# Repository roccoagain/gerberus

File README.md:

# Gerberus

Gerberus checks a PCB design for electrical bugs before you order it: parts pushed past their datasheet limits,
missing protection, swapped pins, parts you can't buy, and bad USB routing. It reads KiCad designs.

## Install

Gerberus is built from source. With [Rust](https://rustup.rs) and git installed:

```sh
git clone https://github.com/roccoagain/gerberus
cd gerberus
cargo install --locked --path .
```

That puts the `gerberus` command in `~/.cargo/bin`. To update, run `git pull` and the same `cargo install` again.

Three commands need another program installed: `gerberus stress` and `gerberus signal` need [ngspice](https://ngspice.sourceforge.io/),
and `gerberus datasheet verify` needs poppler's `pdftotext`. More in [docs/install.md](docs/install.md).

## Quick start

Try it on one of the example boards in the clone:

```sh
cd tests/fixtures/sniffer
gerberus check sniffer.kicad_sch
```

It prints each problem it found, then a count:

```text
error[abs-max]: U1.CE reaches -5.5 V, past the minimum of -0.3 V
  --> U1.CE (+5V), in fault "VIN reversed"
   = help: add a divider, clamp or series resistor, or choose a part rated higher
...
error: 2 errors, 3 warnings, 8 unknown, 102 passed
```

An **error** means a part can be damaged or the board won't work; a **warning** is a risk worth a look. Each one
says what is wrong, where, and how to fix it. **Unknown** means Gerberus couldn't
decide, usually because a part has no part file yet; it never counts as a pass. Add `--all` to list those and the
passes too, and `--verbose` to see the numbers each finding compared, the datasheet pages they came from and how each
net got its voltage range. `gerberus explain abs-max` says what a rule checks and why ([all rules](docs/rules.md)).
The sniffer's 2 errors
are its supply connected backwards, which damages the regulator; its warnings are a regulator input that can sag
below what it needs and headers with no ESD protection.

To see the findings on the drawings, add `--html report.html`: one web page with the schematic and board, each
finding ringed on its part. It needs KiCad's `kicad-cli` on the PATH. [More](docs/html-report.md)

On your own board, point it at the root schematic (`.kicad_sch`). `check` runs
straight away, but without knowing what plugs into the board it can only take the net named GND as 0 V, so most
nets come out unknown. Run `gerberus init` on the schematic to start an `inputs.toml` that says what voltages
arrive on each connector pin (for example, 3.6 to 5.5 V on J1 pin 1). It guesses what it can from net names and
marks each guess for you to check; see [the format](parts/README.md#board-inputs).

To see what to add first, run `gerberus doctor` on the schematic. It lists every part with no part file, every
connector pin nothing describes, and every gap in a part file, ranked by how many unknown results each one
settles. [More](docs/doctor.md)

## What it checks

| Command | What it checks |
| --- | --- |
| `gerberus check` | Every pin against its datasheet limits at its net's worst-case voltage, TVS diodes, capacitor voltage, resistor power, undriven inputs, regulator headroom, junction temperature, ESD protection on connectors, and a supply connected backwards. [More](docs/voltage-checks.md) |
| `gerberus diff` | What changed between two revisions, or against a git tag: parts, connections made or broken, and new or fixed findings. [More](docs/diff.md) |
| `gerberus stress` | Plugging the board in, simulated in SPICE with part tolerances: voltage spikes on every pin. [More](docs/stress.md) |
| `gerberus signal` | Audio and analog signals through the board in SPICE: where an op-amp clips, and what each IC pin sees. [More](docs/signal.md) |
| `gerberus bringup` | A first-power checklist: which supply to connect first, the current limit to set, and the voltage to expect on each rail and where to probe it. [More](docs/bringup.md) |
| `gerberus pinout` | Symbol pins, footprint pads and the datasheet pin table agree. [More](docs/pinout.md) |
| `gerberus bom` | Every part is in stock at LCSC and still listed, with stocked equivalents for short resistors and capacitors. [More](docs/bom.md) |
| `gerberus traces` | Every track wide enough for its net's worst-case current (IPC-2221), every power pin still at its minimum after the copper's voltage drop, a decoupling capacitor near every power pin, no signal crossing a plane split, each switcher's input loop small, SPI/I²S lines short enough for their edges, and thermal reliefs, tombstoning and fiducials for assembly. [More](docs/traces.md) |
| `gerberus si` | USB 2.0 pairs on the board: impedance, skew, vias, stubs, reference planes, and a simulated eye diagram. [More](docs/usb-si.md) |
| `gerberus datasheet` | A part file against its datasheet, value by value. [More](docs/datasheets.md) |

Part limits come from a built-in library of part files, each value cited to its datasheet page. A part with no
part file comes out UNKNOWN rather than PASS. To add one, start it with `gerberus part new <schematic> <reference>`
and fill it in from the datasheet; see [parts/README.md](parts/README.md).

For an AI agent working in a board's repository, `gerberus skill install` adds two skills there: `check-board`
(set up inputs.toml, follow `gerberus doctor`, run the checks) and `datasheet-to-part` (read a datasheet into a
part file, verified against its pages and read twice).

A finding the designers accept on purpose goes in a `waivers.toml` next to the schematic, with the reason; see
[waivers](docs/waivers.md).

Run `gerberus --help` for every command and option.

## Links

- [Docs](docs/README.md): every check in detail.
- [Part file format](parts/README.md).
- [Roadmap](ROADMAP.md).
- [Developing Gerberus](docs/development.md): tests and CI.
- [Example boards](https://github.com/roccoagain/hardware).

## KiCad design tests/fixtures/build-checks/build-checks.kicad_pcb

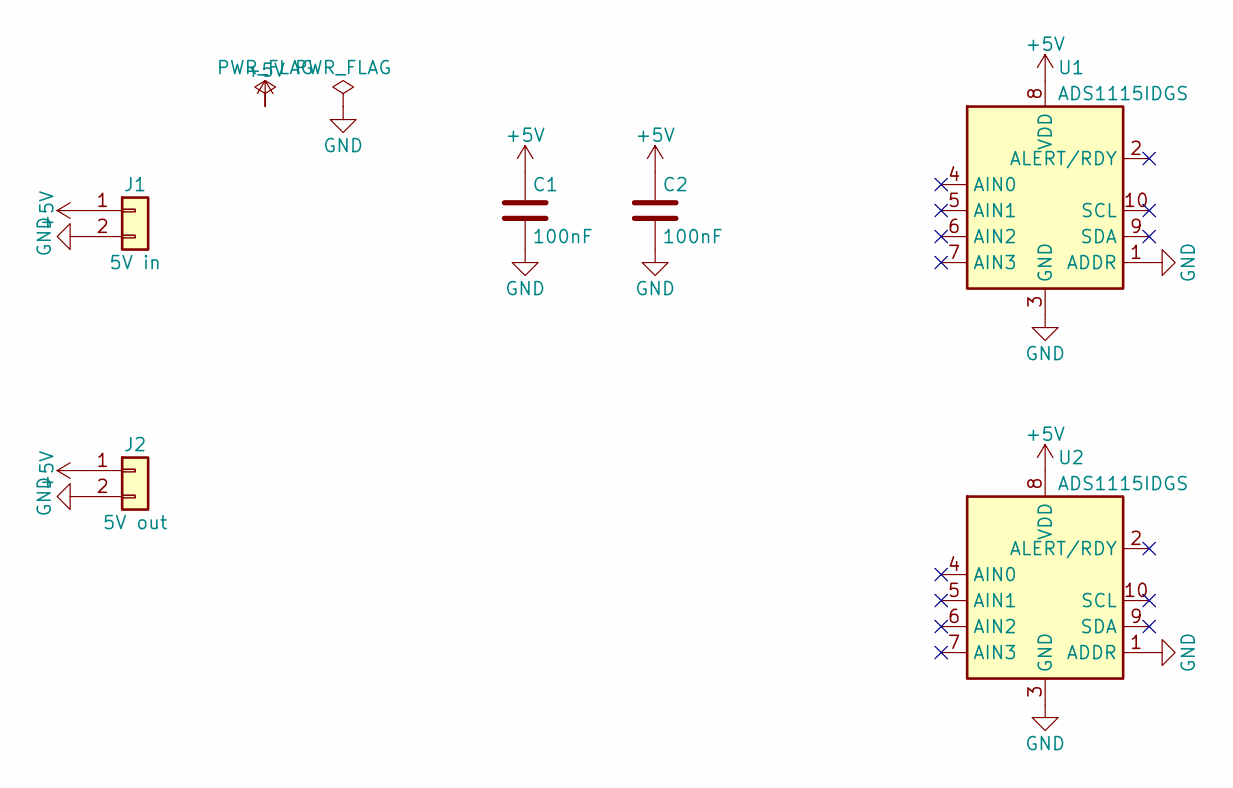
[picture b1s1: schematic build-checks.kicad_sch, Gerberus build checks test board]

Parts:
C1, C2: 100nF; C_0402_1005Metric
J1: 5V in; PinHeader_1x02_P2.54mm_Vertical
J2: 5V out; PinHeader_1x02_P2.54mm_Vertical
U1, U2: ADS1115IDGS; TSSOP-10_3x3mm_P0.5mm

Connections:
+5V: C1.1, C2.1, J1.1, J2.1, U1.8 (VDD), U2.8 (VDD)
GND: C1.2, C2.2, J1.2, J2.2, U1.1 (ADDR), U1.3 (GND), U2.1 (ADDR), U2.3 (GND)

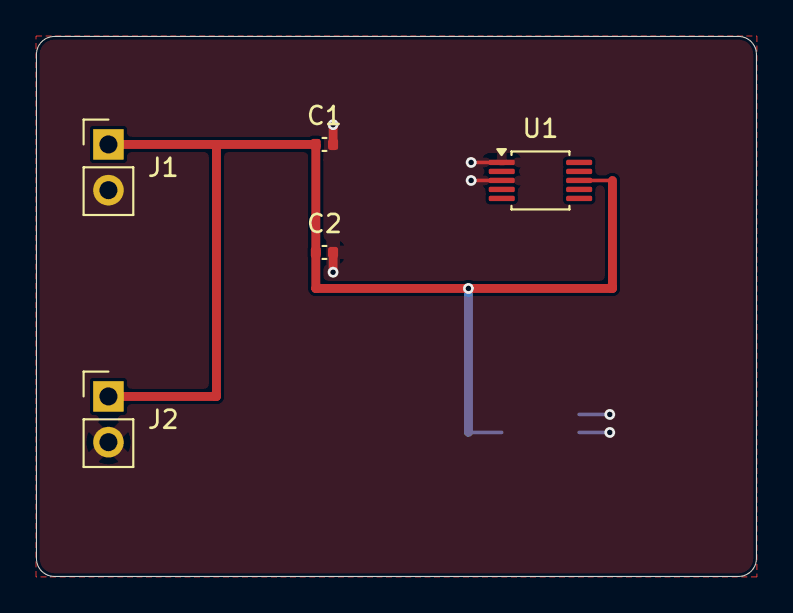
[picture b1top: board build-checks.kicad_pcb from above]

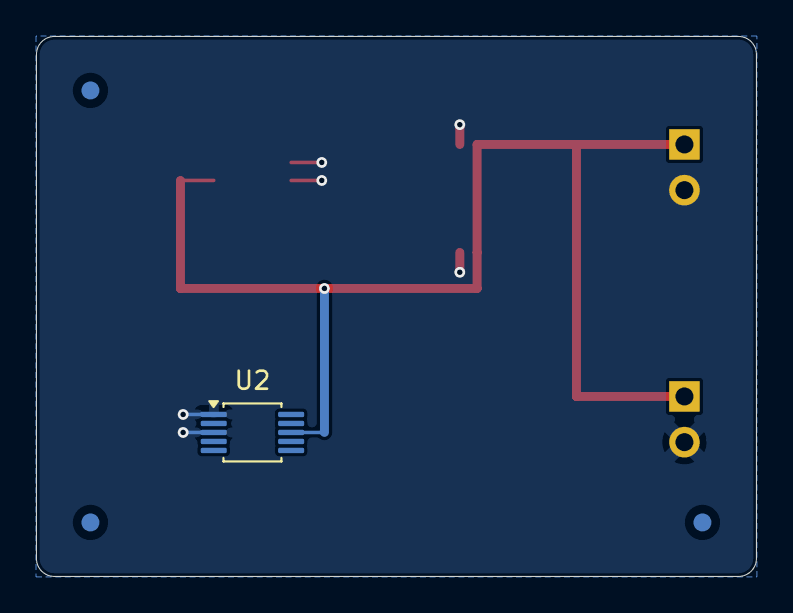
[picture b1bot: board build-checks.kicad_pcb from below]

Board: 2 copper layers, 40.0 x 30.0 mm, 9 parts (4 on the bottom side), 2 nets.

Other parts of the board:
FID1, FID2, FID3: Fiducial_1mm_Mask2mm

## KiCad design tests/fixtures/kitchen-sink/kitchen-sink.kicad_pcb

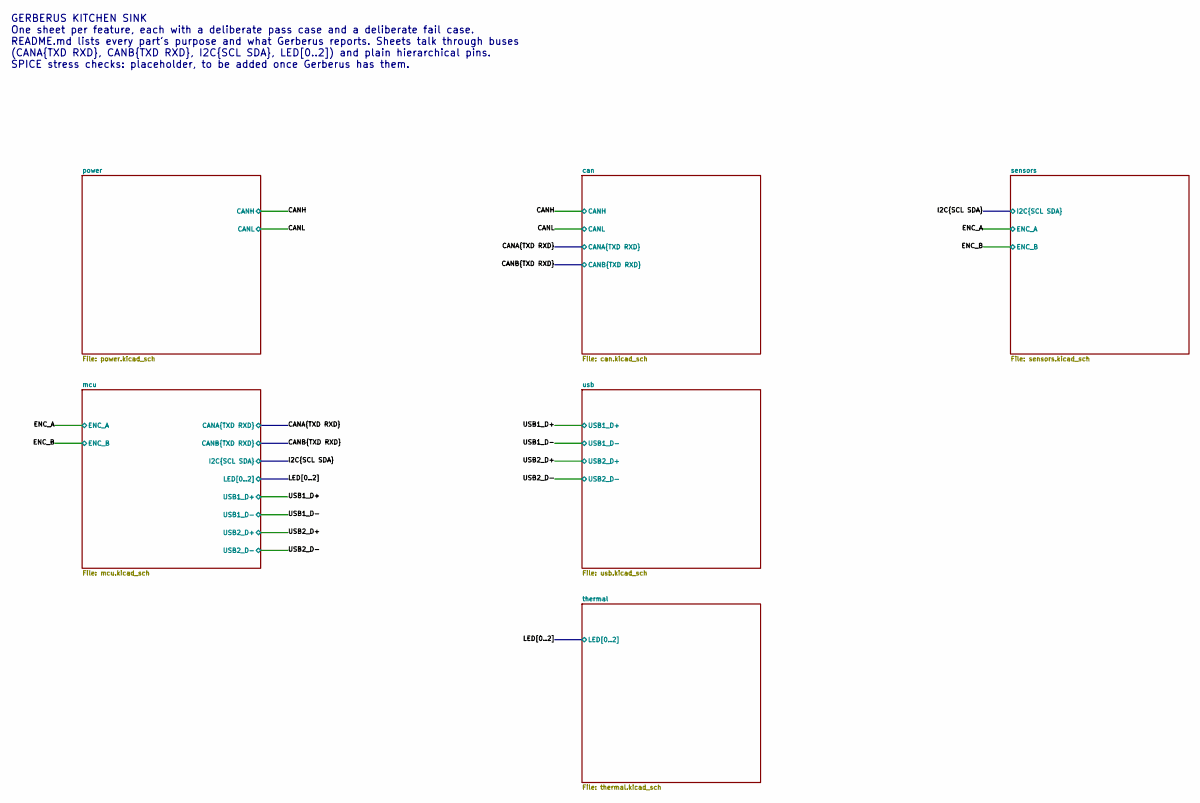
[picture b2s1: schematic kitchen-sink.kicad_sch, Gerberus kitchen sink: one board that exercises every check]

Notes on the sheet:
GERBERUS KITCHEN SINK One sheet per feature, each with a deliberate pass case and a deliberate fail case. README.md lists every part's purpose and what Gerberus reports. Sheets talk through buses (CANA{TXD RXD}, CANB{TXD RXD}, I2C{SCL SDA}, LED[0..2]) and plain hierarchical pins. SPICE stress check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

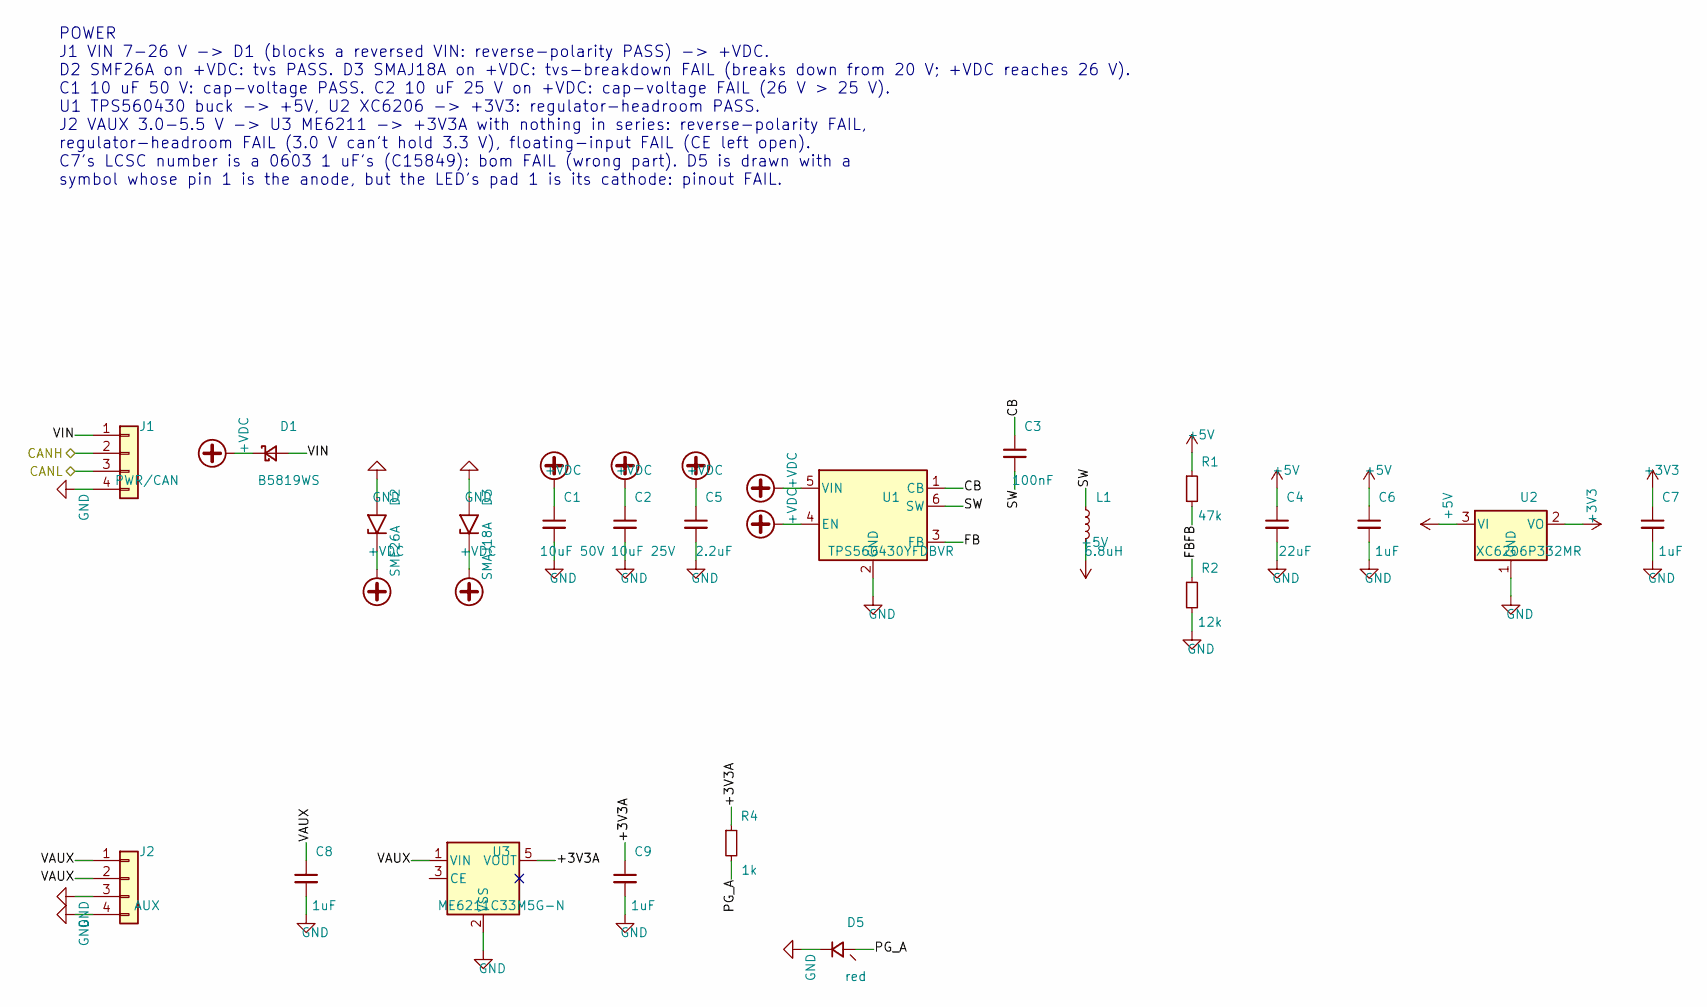
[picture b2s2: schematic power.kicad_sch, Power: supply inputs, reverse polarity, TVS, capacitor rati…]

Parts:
C1: 10uF 50V; C_0805_2012Metric; MPN GRM21BR61H106KE43L; LCSC C440198
C2: 10uF 25V; C_0805_2012Metric; MPN CL21A106KAYNNNE; LCSC C15850
C3: 100nF; C_0402_1005Metric; MPN CL05B104KO5NNNC; LCSC C1525
C4: 22uF; C_0805_2012Metric; MPN CL21A226MAQNNNE; LCSC C45783
C5: 2.2uF; C_0805_2012Metric; MPN CC0805KKX7R9BB225; LCSC C125847
C6, C8, C9: 1uF; C_0402_1005Metric; MPN CL05A105KA5NQNC; LCSC C52923
C7: 1uF; C_0402_1005Metric; MPN CL05A105KA5NQNC; LCSC C15849
D1: B5819WS; D_SOD-323; MPN B5819WS; LCSC C22624
D2: SMF26A; D_SOD-123F; MPN SMF26A; LCSC C123789
D3: SMAJ18A; D_SMA; MPN SMAJ18A; LCSC C173513
D5: red; LED_0603_1608Metric; MPN KT-0603R; LCSC C2286
J1: PWR/CAN; JST_GH_SM04B-GHS-TB_1x04-1MP_P1.25mm_Horizontal; MPN SM04B-GHS-TB(LF)(SN); LCSC C189895
J2: AUX; JST_SH_SM04B-SRSS-TB_1x04-1MP_P1.00mm_Horizontal; MPN SM04B-SRSS-TB(LF)(SN); LCSC C160404
L1: 6.8uH; L_Changjiang_FNR4030S; MPN FNR4030S6R8MT; LCSC C167876
R1: 47k; R_0402_1005Metric; MPN 0402WGF4702TCE; LCSC C25792
R2: 12k; R_0402_1005Metric; MPN 0402WGF1202TCE; LCSC C25752
R4: 1k; R_0603_1608Metric; MPN 0603WAF1001T5E; LCSC C21190
U1: TPS560430YFDBVR; SOT-23-6; MPN TPS560430YFDBVR; LCSC C962155
U2: XC6206P332MR; SOT-23-3; MPN XC6206P332MR-G; LCSC C5446
U3: ME6211C33M5G-N; SOT-23-5; MPN ME6211C33M5G-N; LCSC C82942

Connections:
+3V3: C7.1, U2.2 (VO); also elsewhere on the board
+5V: C4.1, C6.1, L1.2, R1.1, U2.3 (VI); also elsewhere on the board
+VDC: C1.1, C2.1, C5.1, D1.1 (K), D2.1 (A1), D3.1 (A1), U1.4 (EN), U1.5 (VIN); also elsewhere on the board
/CANH: J1.2; also elsewhere on the board
/CANL: J1.3; also elsewhere on the board
/power/+3V3A: C9.1, R4.1, U3.5 (VOUT)
/power/CB: C3.1, U1.1 (CB)
/power/FB: R1.2, R2.1, U1.3 (FB)
/power/PG_A: D5.1 (A), R4.2
/power/SW: C3.2, L1.1, U1.6 (SW)
/power/VAUX: C8.1, J2.1, J2.2, U3.1 (VIN)
/power/VIN: D1.2 (A), J1.1
GND: C1.2, C2.2, C4.2, C5.2, C6.2, C7.2, C8.2, C9.2, D2.2 (A2), D3.2 (A2), D5.2 (K), J1.4, J2.3, J2.4, R2.2, U1.2 (GND), U2.1 (GND), U3.2 (VSS); also elsewhere on the board

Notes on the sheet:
POWER J1 VIN 7-26 V -> D1 (blocks a reversed VIN: reverse-polarity PASS) -> +VDC. D2 SMF26A on +VDC: tvs PASS. D3 SMAJ18A on +VDC: tvs-breakdown FAIL (breaks down from 20 V; +VDC reaches 26 V). C1 10 uF 50 V: cap-voltage PASS. C2 10 uF 25 V on +VDC: cap-voltage FAIL (26 V > 25 V). U1 TPS560430 buck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

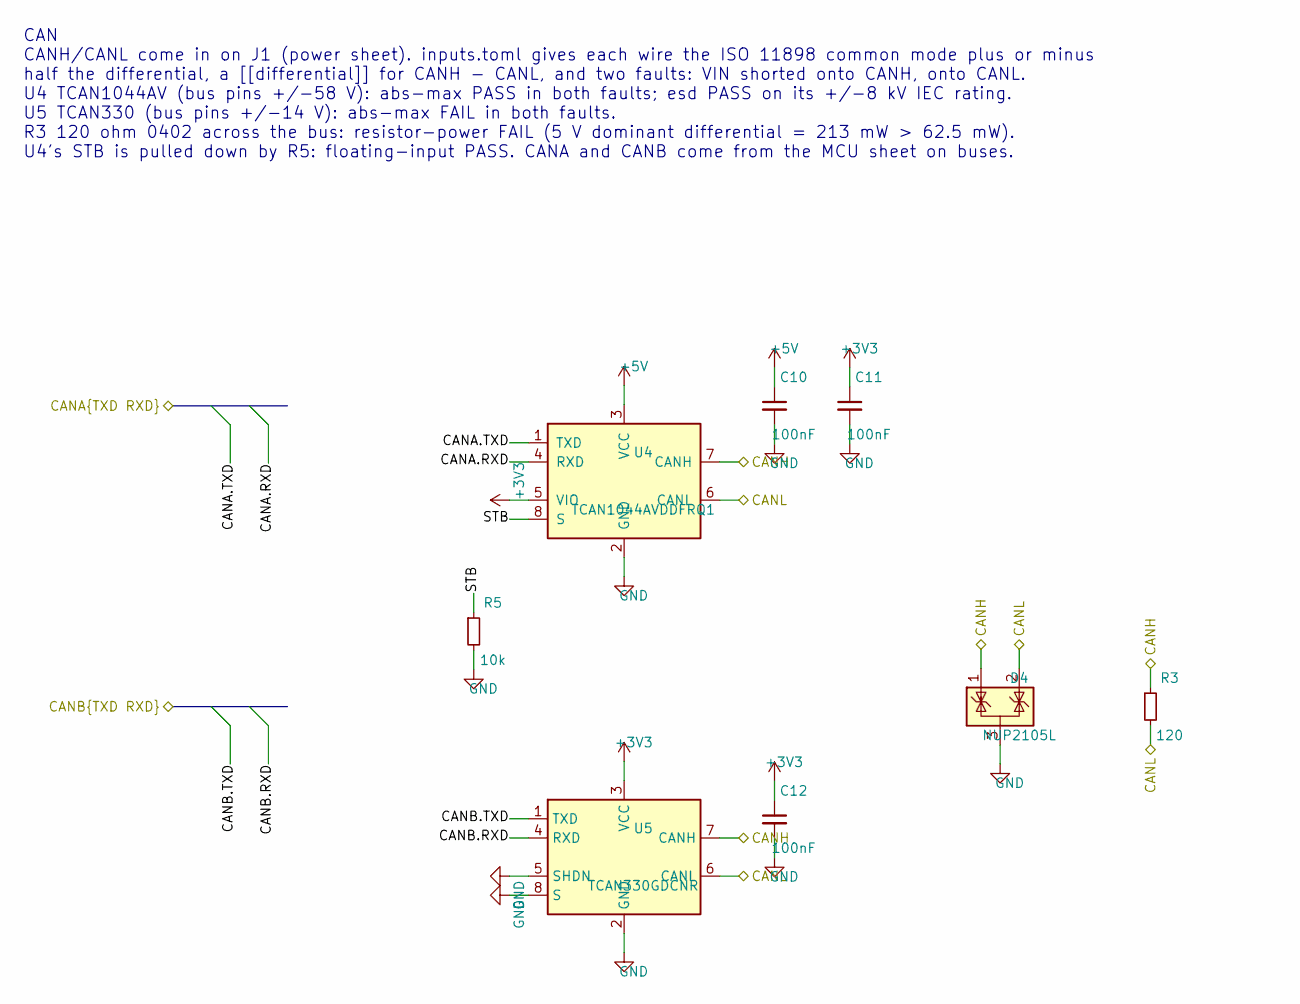
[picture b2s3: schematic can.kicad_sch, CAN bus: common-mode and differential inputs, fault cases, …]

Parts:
C10, C11, C12: 100nF; C_0402_1005Metric; MPN CL05B104KO5NNNC; LCSC C1525
D4: NUP2105L; SOT-23; MPN NUP2105LT1G; LCSC C14486
R3: 120; R_0402_1005Metric; MPN 0402WGF1200TCE; LCSC C25079
R5: 10k; R_0402_1005Metric; MPN 0402WGF1002TCE; LCSC C25744
U4: TCAN1044AVDDFRQ1; SOT-23-8; MPN TCAN1044AVDDFRQ1; LCSC C3236207
U5: TCAN330GDCNR; SOT-23-8; MPN TCAN330GDCNR; LCSC C191006

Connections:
+3V3: C11.1, C12.1, U4.5 (VIO), U5.3 (VCC); also elsewhere on the board
+5V: C10.1, U4.3 (VCC); also elsewhere on the board
/CANA.RXD: U4.4 (RXD); also elsewhere on the board
/CANA.TXD: U4.1 (TXD); also elsewhere on the board
/CANB.RXD: U5.4 (RXD); also elsewhere on the board
/CANB.TXD: U5.1 (TXD); also elsewhere on the board
/CANH: D4.1 (K), R3.1, U4.7 (CANH), U5.7 (CANH); also elsewhere on the board
/CANL: D4.2 (K), R3.2, U4.6 (CANL), U5.6 (CANL); also elsewhere on the board
/can/STB: R5.1, U4.8 (S)
GND: C10.2, C11.2, C12.2, D4.3 (A), R5.2, U4.2 (GND), U5.2 (GND), U5.5 (SHDN), U5.8 (S); also elsewhere on the board

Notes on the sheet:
CAN CANH/CANL come in on J1 (power sheet). inputs.toml gives each wire the ISO 11898 common mode plus or minus half the differential, a [[differential]] for CANH - CANL, and two faults: VIN shorted onto CANH, onto CANL. U4 TCAN1044AV (bus pins +/-58 V): abs-max PASS in both faults; esd PASS on its 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

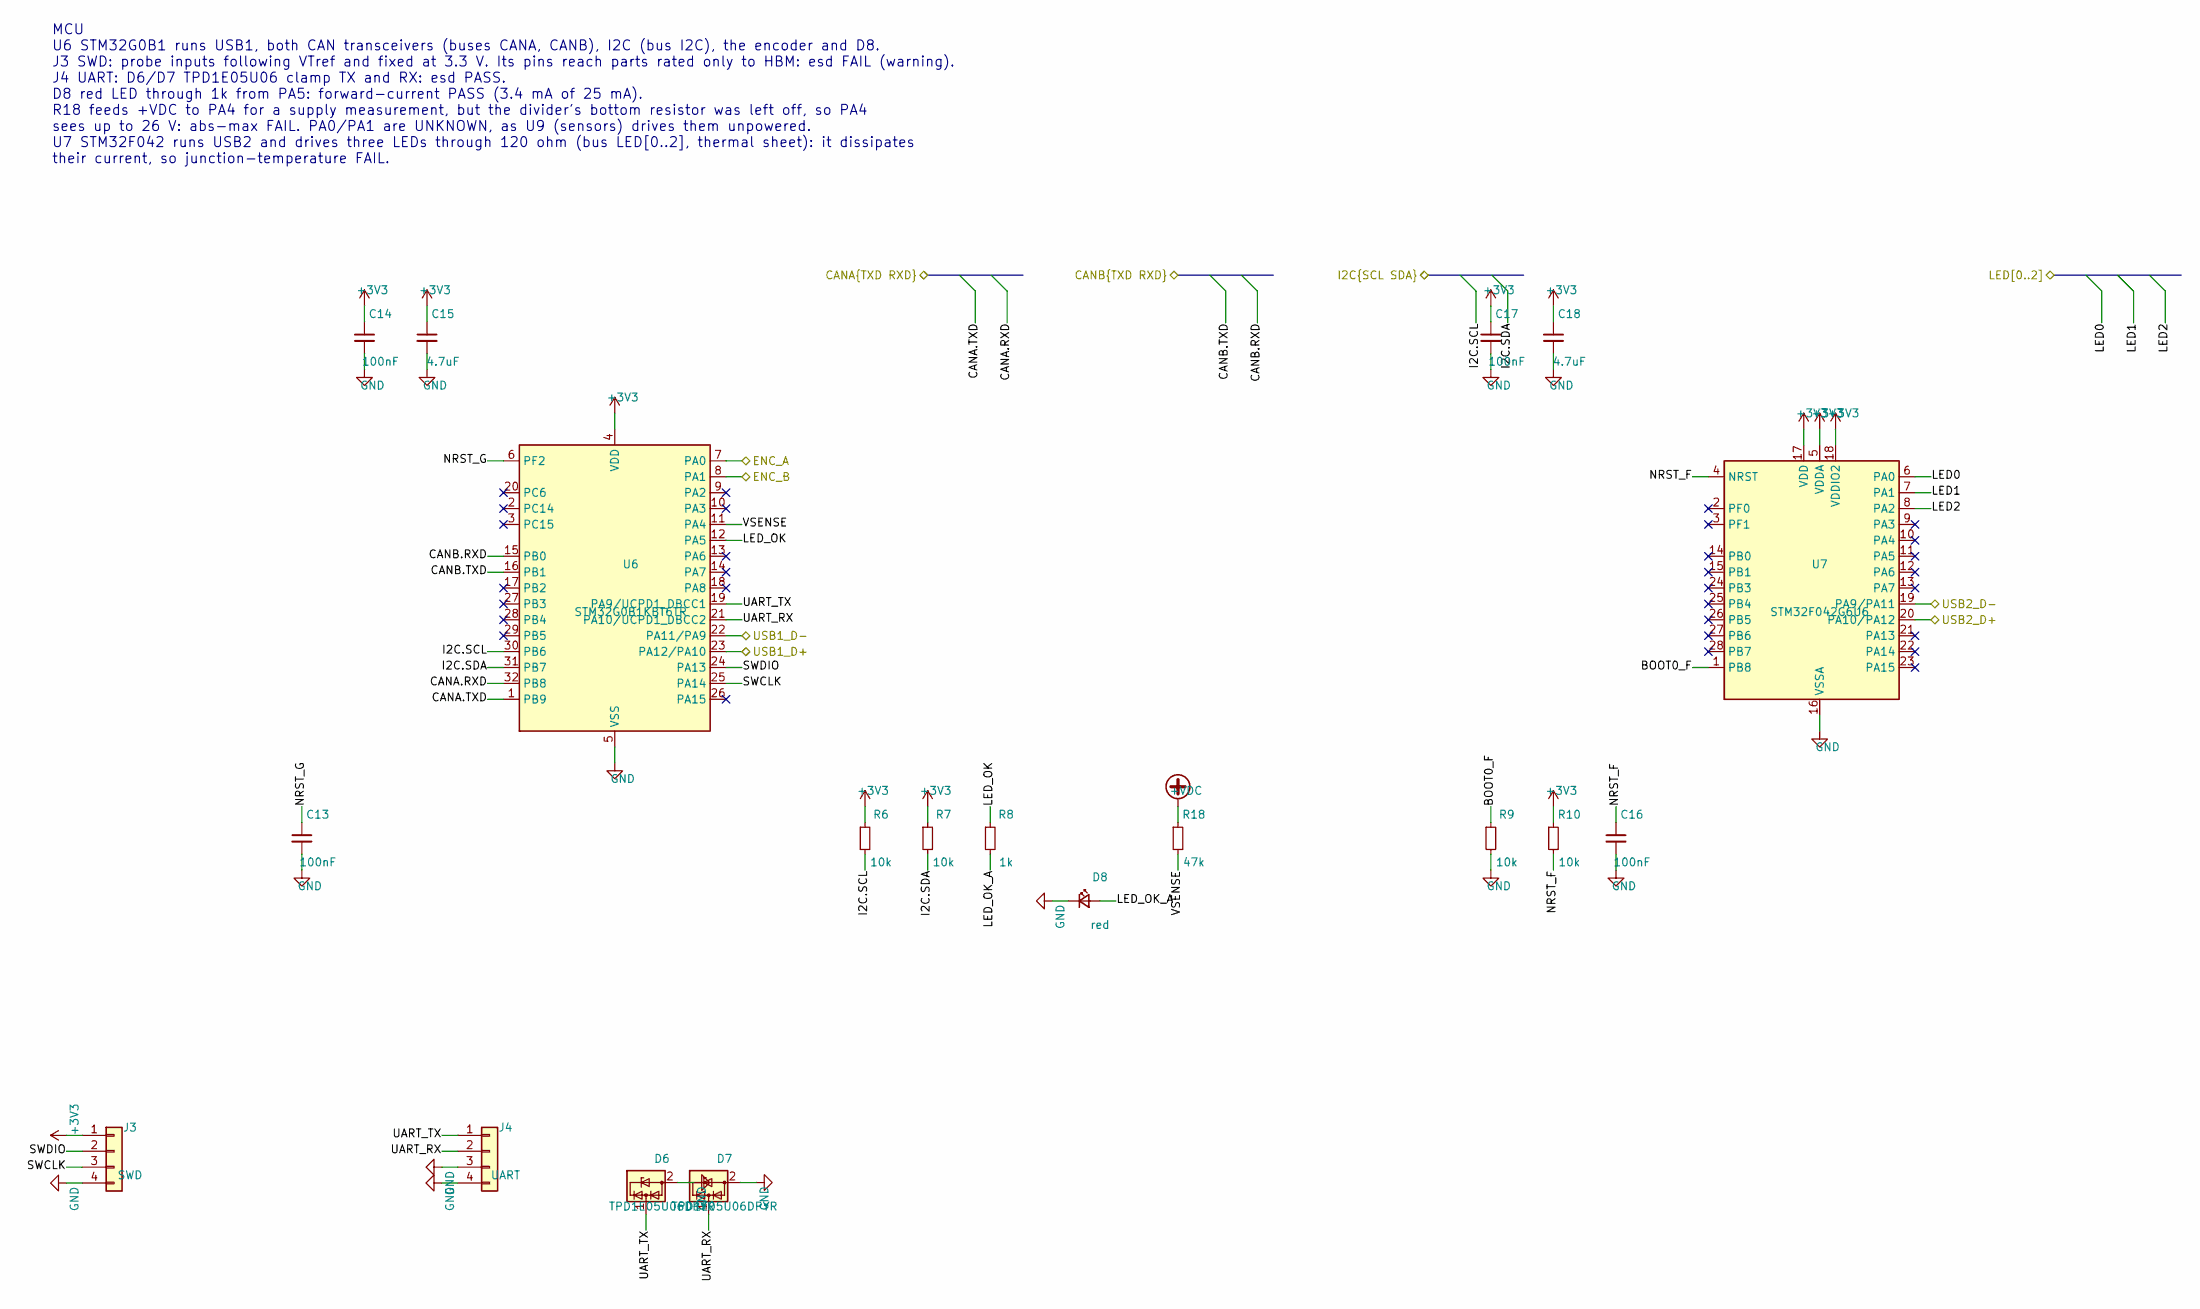
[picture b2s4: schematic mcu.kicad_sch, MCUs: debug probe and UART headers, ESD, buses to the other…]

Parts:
C13, C14, C16, C17: 100nF; C_0402_1005Metric; MPN CL05B104KO5NNNC; LCSC C1525
C15, C18: 4.7uF; C_0603_1608Metric; MPN CL10A475KO8NNNC; LCSC C19666
D6, D7: TPD1E05U06DPYR; Texas_DPY0002A_0.6x1mm_P0.65mm; MPN TPD1E05U06DPYR; LCSC C436349
D8: red; LED_0603_1608Metric; MPN KT-0603R; LCSC C2286
J3: SWD; JST_SH_SM04B-SRSS-TB_1x04-1MP_P1.00mm_Horizontal; MPN SM04B-SRSS-TB(LF)(SN); LCSC C160404
J4: UART; JST_SH_SM04B-SRSS-TB_1x04-1MP_P1.00mm_Horizontal; MPN SM04B-SRSS-TB(LF)(SN); LCSC C160404
R6, R7, R9, R10: 10k; R_0603_1608Metric; MPN 0603WAF1002T5E; LCSC C25804
R8: 1k; R_0603_1608Metric; MPN 0603WAF1001T5E; LCSC C21190
R18: 47k; R_0402_1005Metric; MPN 0402WGF4702TCE; LCSC C25792
U6: STM32G0B1KBT6TR; LQFP-32_7x7mm_P0.8mm; MPN STM32G0B1KBT6TR; LCSC C7021416
U7: STM32F042G6U6; QFN-28_4x4mm_P0.5mm; MPN STM32F042G6U6TR; LCSC C2971720

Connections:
+3V3: C14.1, C15.1, C17.1, C18.1, J3.1, R6.1, R7.1, R10.1, U6.4 (VDD), U7.5 (VDDA), U7.17 (VDD), U7.18 (VDDIO2); also elsewhere on the board
+VDC: R18.1; also elsewhere on the board
/CANA.RXD: U6.32 (PB8); also elsewhere on the board
/CANA.TXD: U6.1 (PB9); also elsewhere on the board
/CANB.RXD: U6.15 (PB0); also elsewhere on the board
/CANB.TXD: U6.16 (PB1); also elsewhere on the board
/ENC_A: U6.7 (PA0); also elsewhere on the board
/ENC_B: U6.8 (PA1); also elsewhere on the board
/I2C.SCL: R6.2, U6.30 (PB6); also elsewhere on the board
/I2C.SDA: R7.2, U6.31 (PB7); also elsewhere on the board
/LED0: U7.6 (PA0); also elsewhere on the board
/LED1: U7.7 (PA1); also elsewhere on the board
/LED2: U7.8 (PA2); also elsewhere on the board
/USB1_D+: U6.23 (PA12/PA10); also elsewhere on the board
/USB1_D-: U6.22 (PA11/PA9); also elsewhere on the board
/USB2_D+: U7.20 (PA10/PA12); also elsewhere on the board
/USB2_D-: U7.19 (PA9/PA11); also elsewhere on the board
/mcu/BOOT0_F: R9.1, U7.1 (PB8)
/mcu/LED_OK: R8.1, U6.12 (PA5)
/mcu/LED_OK_A: D8.2 (A), R8.2
/mcu/NRST_F: C16.1, R10.2, U7.4 (NRST)
/mcu/NRST_G: C13.1, U6.6 (PF2)
/mcu/SWCLK: J3.3, U6.25 (PA14)
/mcu/SWDIO: J3.2, U6.24 (PA13)
/mcu/UART_RX: D7.1 (I/O), J4.2, U6.21 (PA10/UCPD1_DBCC2)
/mcu/UART_TX: D6.1 (I/O), J4.1, U6.19 (PA9/UCPD1_DBCC1)
/mcu/VSENSE: R18.2, U6.11 (PA4)
GND: C13.2, C14.2, C15.2, C16.2, C17.2, C18.2, D6.2 (GND), D7.2 (GND), D8.1 (K), J3.4, J4.3, J4.4, R9.2, U6.5 (VSS), U7.16 (VSSA); also elsewhere on the board

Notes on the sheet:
MCU U6 STM32G0B1 runs USB1, both CAN transceivers (buses CANA, CANB), I2C (bus I2C), the encoder and D8. J3 SWD: probe inputs following VTref and fixed at 3.3 V. Its pins reach parts rated only to HBM: esd FAIL (warning). J4 UART: D6/D7 TPD1E05U06 clamp TX and RX: esd PASS. D8 red LED through 1k fr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

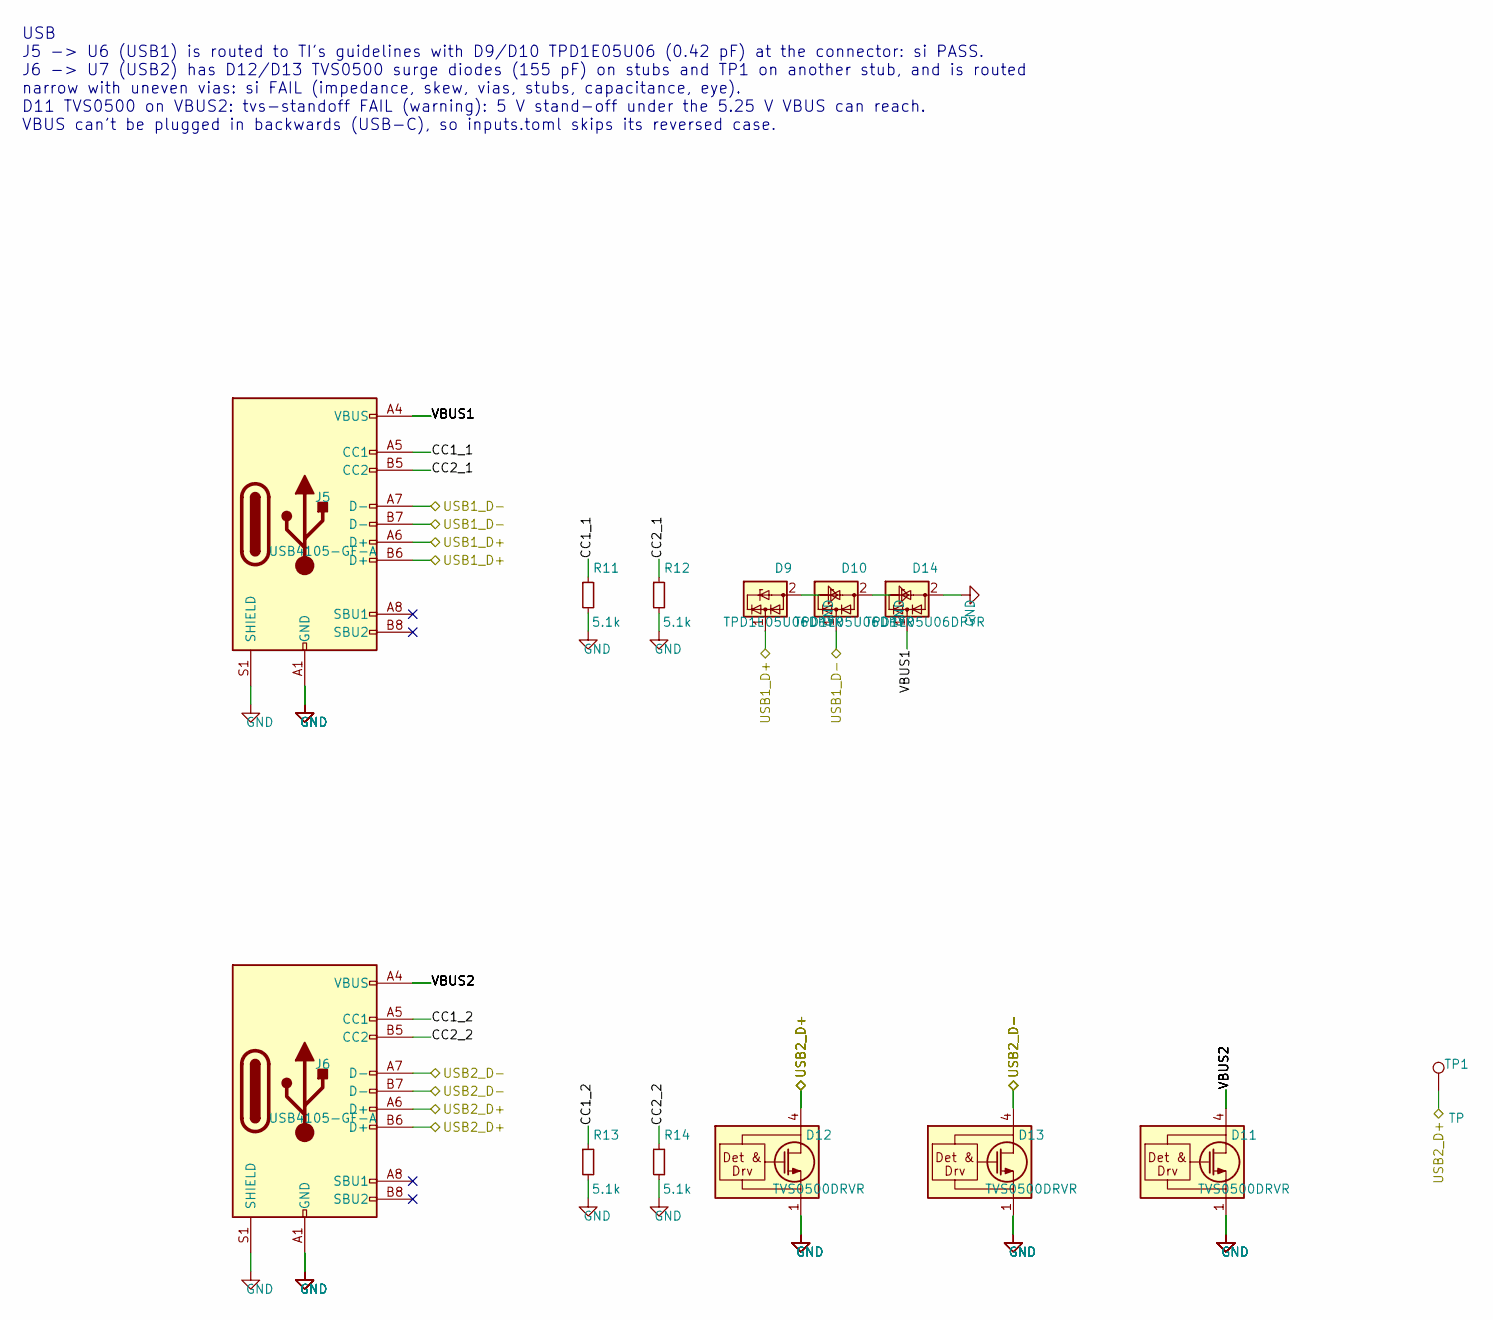
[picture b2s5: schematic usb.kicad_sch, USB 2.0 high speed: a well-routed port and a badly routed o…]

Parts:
D9, D10, D14: TPD1E05U06DPYR; Texas_DPY0002A_0.6x1mm_P0.65mm; MPN TPD1E05U06DPYR; LCSC C436349
D11, D12, D13: TVS0500DRVR; WSON-6-1EP_2x2mm_P0.65mm_EP1x1.6mm; MPN TVS0500DRVR; LCSC C609571
J5, J6: USB4105-GF-A; USB_C_Receptacle_GCT_USB4105-xx-A_16P_TopMnt_Horizontal; MPN USB4105-GF-A; LCSC C3020560
R11, R12, R13, R14: 5.1k; R_0402_1005Metric; MPN 0402WGF5101TCE; LCSC C25905
TP1: TP; TestPoint_Pad_D1.0mm

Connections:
/USB1_D+: D9.1 (I/O), J5.A6 (D+), J5.B6 (D+); also elsewhere on the board
/USB1_D-: D10.1 (I/O), J5.A7 (D-), J5.B7 (D-); also elsewhere on the board
/USB2_D+: D12.4 (IN), D12.5 (IN), D12.6 (IN), J6.A6 (D+), J6.B6 (D+), TP1.1; also elsewhere on the board
/USB2_D-: D13.4 (IN), D13.5 (IN), D13.6 (IN), J6.A7 (D-), J6.B7 (D-); also elsewhere on the board
/usb/CC1_1: J5.A5 (CC1), R11.1
/usb/CC1_2: J6.A5 (CC1), R13.1
/usb/CC2_1: J5.B5 (CC2), R12.1
/usb/CC2_2: J6.B5 (CC2), R14.1
/usb/VBUS1: D14.1 (I/O), J5.A4 (VBUS), J5.A9 (VBUS), J5.B4 (VBUS), J5.B9 (VBUS)
/usb/VBUS2: D11.4 (IN), D11.5 (IN), D11.6 (IN), J6.A4 (VBUS), J6.A9 (VBUS), J6.B4 (VBUS), J6.B9 (VBUS)
GND: D9.2 (GND), D10.2 (GND), D11.1 (GND), D11.2 (GND), D11.3 (GND), D11.7 (GND), D12.1 (GND), D12.2 (GND), D12.3 (GND), D12.7 (GND), D13.1 (GND), D13.2 (GND), D13.3 (GND), D13.7 (GND), D14.2 (GND), J5.A1 (GND), J5.A12 (GND), J5.B1 (GND), J5.B12 (GND), J5.S1 (SHIELD), J6.A1 (GND), J6.A12 (GND), J6.B1 (GND), J6.B12 (GND), J6.S1 (SHIELD), R11.2, R12.2, R13.2, R14.2; also elsewhere on the board

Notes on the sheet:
USB J5 -> U6 (USB1) is routed to TI's guidelines with D9/D10 TPD1E05U06 (0.42 pF) at the connector: si PASS. J6 -> U7 (USB2) has D12/D13 TVS0500 surge diodes (155 pF) on stubs and TP1 on another stub, and is routed narrow with uneven vias: si FAIL (impedance, skew, vias, stubs, capacitance, eye). D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

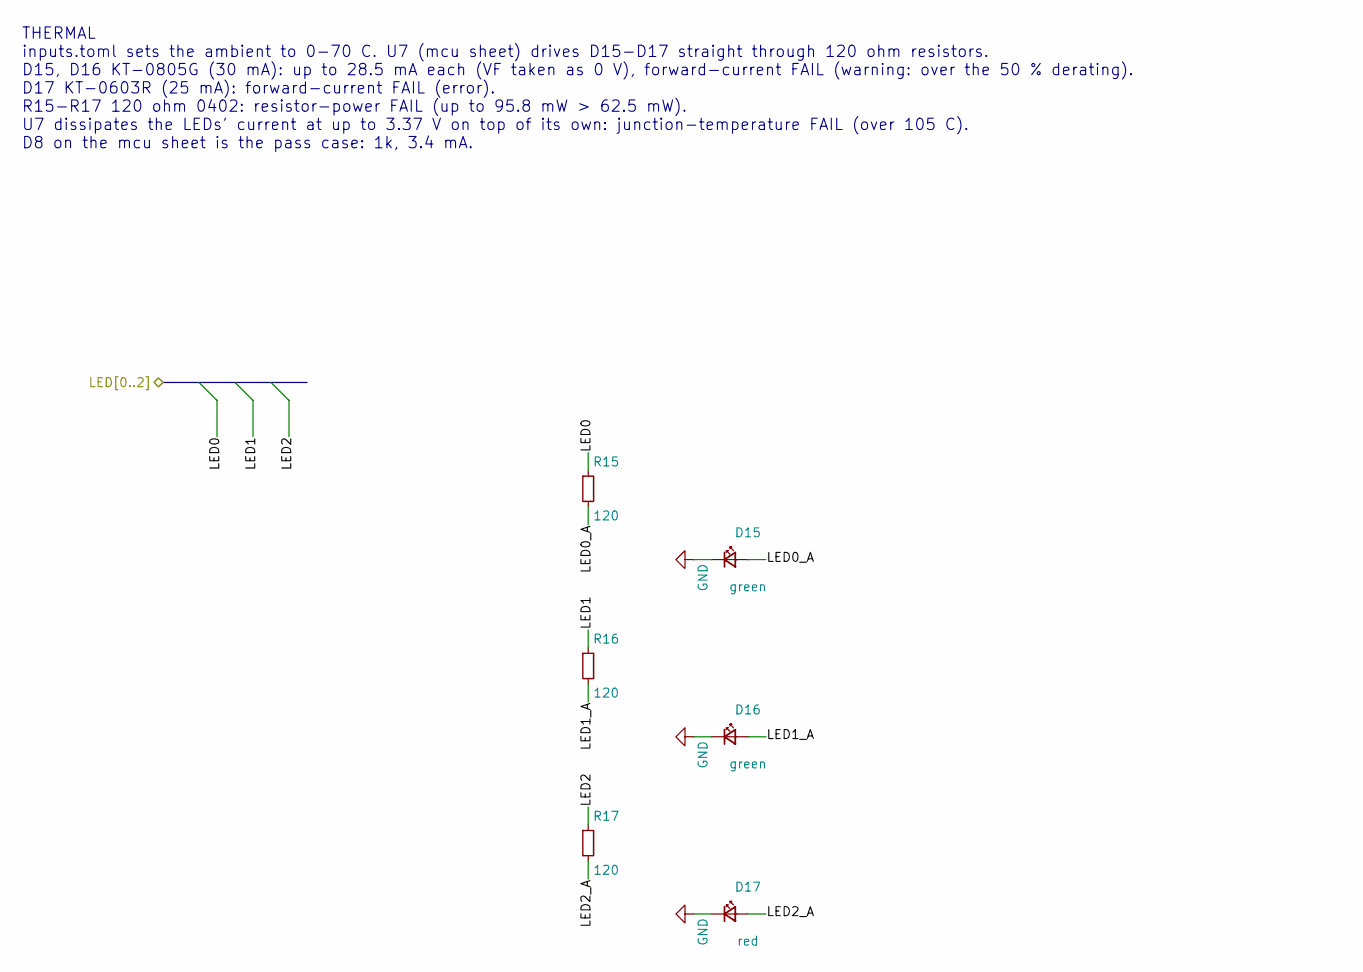
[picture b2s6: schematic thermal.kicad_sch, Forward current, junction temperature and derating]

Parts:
D15, D16: green; LED_0805_2012Metric; MPN KT-0805G; LCSC C2297
D17: red; LED_0603_1608Metric; MPN KT-0603R; LCSC C2286
R15, R16, R17: 120; R_0402_1005Metric; MPN 0402WGF1200TCE; LCSC C25079

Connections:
/LED0: R15.1; also elsewhere on the board
/LED1: R16.1; also elsewhere on the board
/LED2: R17.1; also elsewhere on the board
/thermal/LED0_A: D15.2 (A), R15.2
/thermal/LED1_A: D16.2 (A), R16.2
/thermal/LED2_A: D17.2 (A), R17.2
GND: D15.1 (K), D16.1 (K), D17.1 (K); also elsewhere on the board

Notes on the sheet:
THERMAL inputs.toml sets the ambient to 0-70 C. U7 (mcu sheet) drives D15-D17 straight through 120 ohm resistors. D15, D16 KT-0805G (30 mA): up to 28.5 mA each (VF taken as 0 V), forward-current FAIL (warning: over the 50 % derating). D17 KT-0603R (25 mA): forward-current FAIL (error). R15-R17 120 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

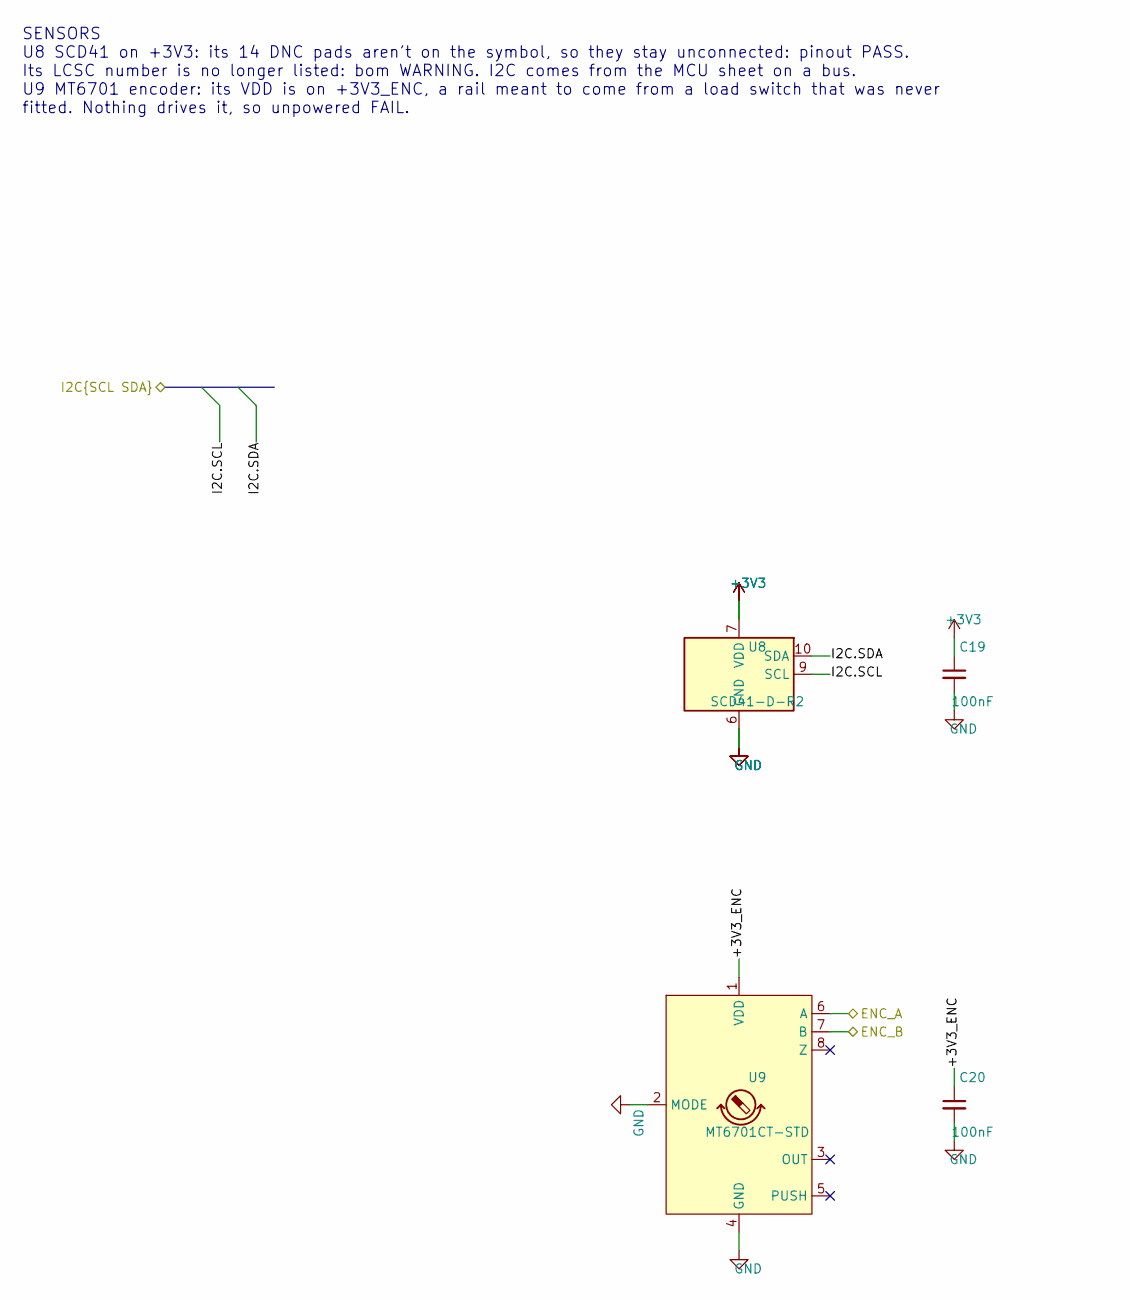
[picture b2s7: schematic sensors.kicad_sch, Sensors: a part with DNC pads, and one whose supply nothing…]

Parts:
C19, C20: 100nF; C_0402_1005Metric; MPN CL05B104KO5NNNC; LCSC C1525
U8: SCD41-D-R2; Sensirion_SCD4x-1EP_10.1x10.1mm_P1.25mm_EP4.8x4.8mm; MPN SCD41-D-R2; LCSC C3659294
U9: MT6701CT-STD; SOIC-8_3.9x4.9mm_P1.27mm; MPN MT6701CT-STD-R; LCSC C3003196

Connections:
+3V3: C19.1, U8.7 (VDD), U8.19 (VDD); also elsewhere on the board
/ENC_A: U9.6 (A); also elsewhere on the board
/ENC_B: U9.7 (B); also elsewhere on the board
/I2C.SCL: U8.9 (SCL); also elsewhere on the board
/I2C.SDA: U8.10 (SDA); also elsewhere on the board
/sensors/+3V3_ENC: C20.1, U9.1 (VDD)
GND: C19.2, C20.2, U8.6 (GND), U8.20 (GND), U8.21 (GND), U9.2 (MODE), U9.4 (GND); also elsewhere on the board

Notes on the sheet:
SENSORS U8 SCD41 on +3V3: its 14 DNC pads aren't on the symbol, so they stay unconnected: pinout PASS. Its LCSC number is no longer listed: bom WARNING. I2C comes from the MCU sheet on a bus. U9 MT6701 encoder: its VDD is on +3V3_ENC, a rail meant to come from a load switch that was never fitted. N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

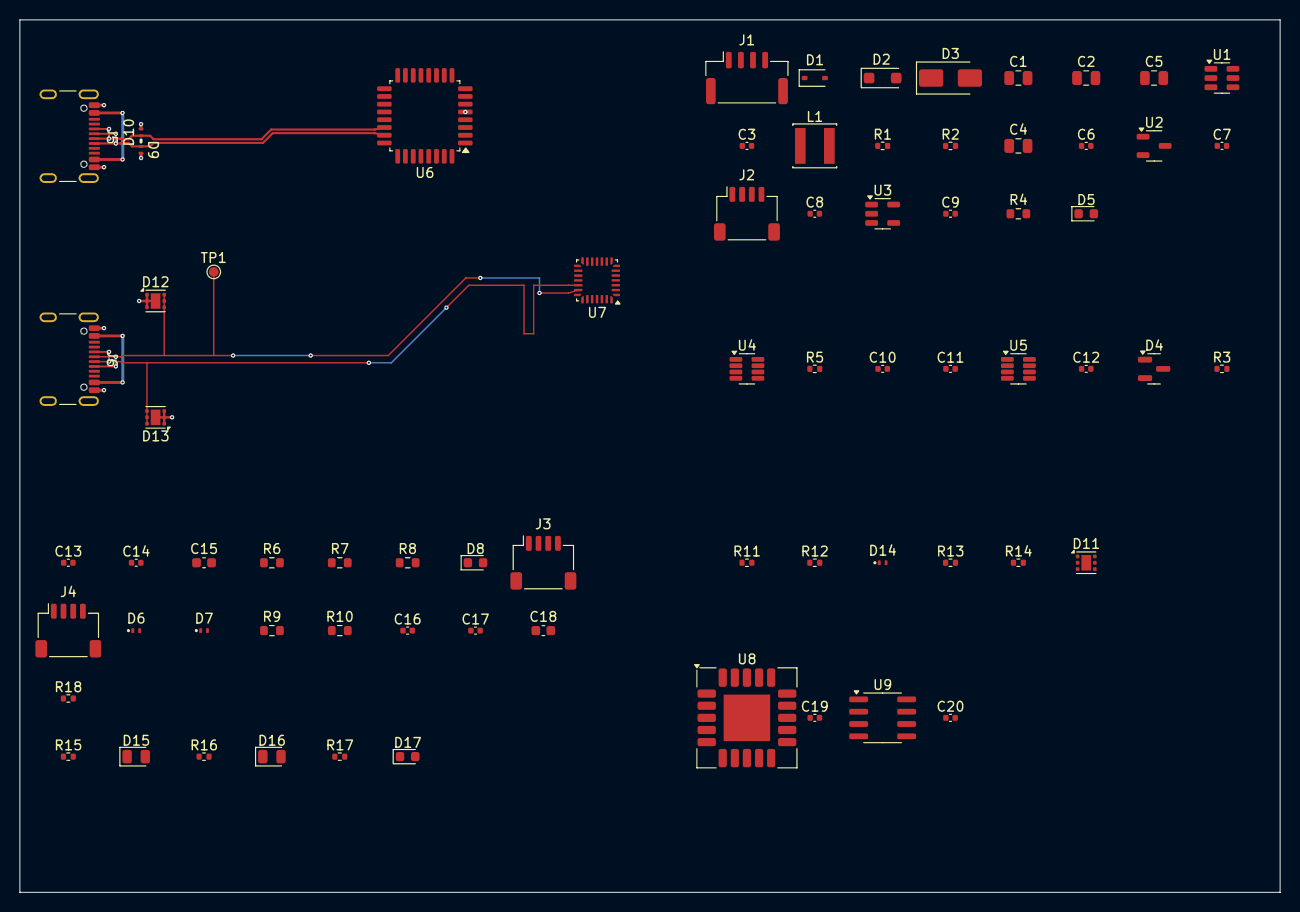
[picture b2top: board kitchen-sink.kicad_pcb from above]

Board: 4 copper layers, 130.0 x 90.0 mm, 72 parts (0 on the bottom side), 49 nets.
